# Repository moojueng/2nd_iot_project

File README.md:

# 2nd_iot_project
Portfolio for student 

arduino, Raspberry Pi, atmega328, atmega128, flask, mariaDB

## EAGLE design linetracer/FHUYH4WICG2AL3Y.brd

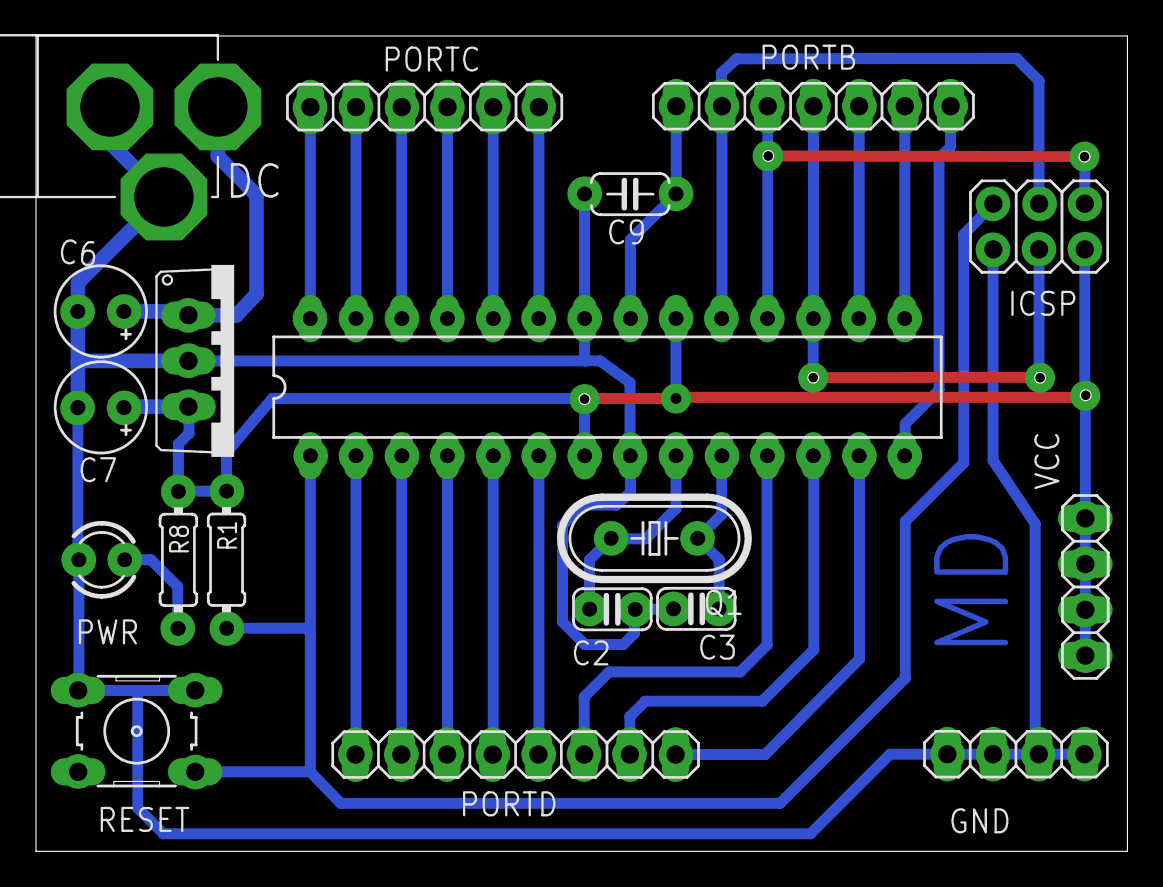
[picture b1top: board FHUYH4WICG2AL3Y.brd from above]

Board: 2 copper layers, 60.6 x 45.3 mm, 19 parts (0 on the bottom side), 28 nets.

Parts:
BVALUE: ATMEGA168; DIL28-3
C2, C3: 22pf; C025-024X044
C6, C7: 47u; E2,5-5
C9: 100n; C050-024X044
DC: 9V in; DC-21MM
GND: 1X04
ICSP: ICSP; 2X03
PORTB: 1X07
PORTC: 1X06
PORTD: 1X08
PWR: LED3MM
Q1: 20Mhz; HC49U-V
R1: 10k; 0204/7
R8: 330; 0204/7
REG: 7805; TO220V
RESET: B3F-10XX
VCC: 1X04

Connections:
+5V: BVALUE.7, C7.+, ICSP.2, R1.2, R8.1, REG.3, VCC.1, VCC.2, VCC.3, VCC.4
AREF: BVALUE.21, C9.1
GND: GND.1, GND.2, GND.3, GND.4, RESET.3, RESET.4
unnamed: BVALUE.15, PORTB.6
unnamed: PWR.A, R8.2
unnamed: BVALUE.9, C2.2, Q1.2
unnamed: BVALUE.4, PORTD.3
unnamed: BVALUE.5, PORTD.4
unnamed: BVALUE.6, PORTD.5
unnamed: BVALUE.11, PORTD.6
unnamed: BVALUE.12, PORTD.7
unnamed: BVALUE.13, PORTD.8
unnamed: BVALUE.23, PORTC.1
unnamed: BVALUE.24, PORTC.2
unnamed: BVALUE.25, PORTC.3
unnamed: BVALUE.26, PORTC.4
unnamed: BVALUE.27, PORTC.5
unnamed: BVALUE.28, PORTC.6
unnamed: BVALUE.3, PORTD.2
unnamed: BVALUE.16, PORTB.5
unnamed: ICSP.1, PORTB.3
unnamed: BVALUE.10, C3.2, Q1.1
unnamed: BVALUE.17, ICSP.4, PORTB.4
unnamed: BVALUE.2, PORTD.1
RESET: BVALUE.1, ICSP.5, R1.1, RESET.1
S$1: BVALUE.8, BVALUE.22, C2.1, C6.-, C7.-, C9.2, DC.1, DC.3, PWR.K, REG.2
SCK: BVALUE.19, ICSP.3, PORTB.2
VIN: C6.+, DC.2, REG.1

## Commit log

2024-04-22 2nd_iot_project
